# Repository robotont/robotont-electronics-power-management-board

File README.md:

# robotont-electronics-power-management-board
The repository contains schematics and PCB layout for the Robotont power management board.
The [production](Production/) folder contains prepared gerbers with pos file ready to order a from e.g. JLCPCB.

## Schematics

## Layout

The following figures visualize the front side of the board along with the 3D model of the design.

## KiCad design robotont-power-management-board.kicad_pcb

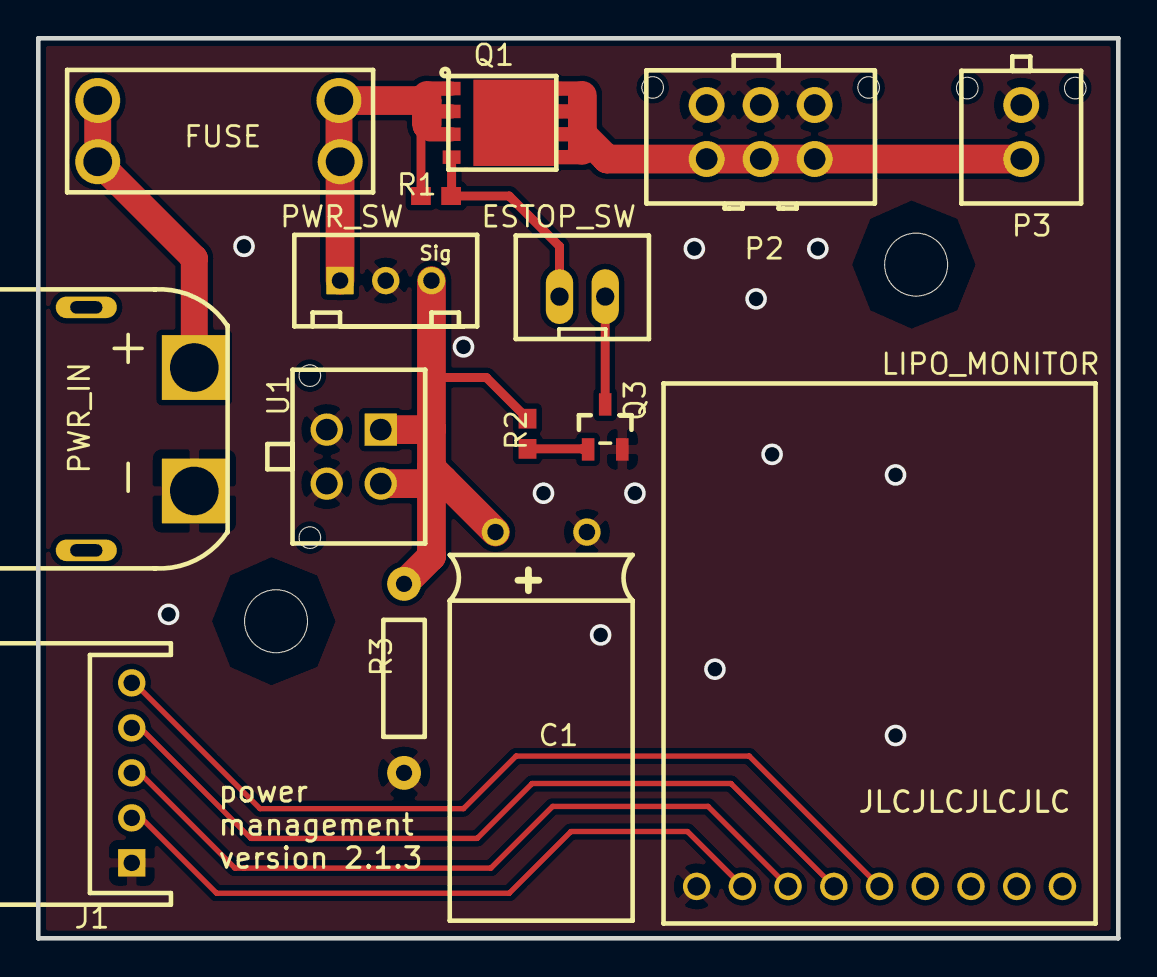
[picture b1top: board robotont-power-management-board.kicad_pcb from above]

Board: 2 copper layers, 60.0 x 50.0 mm, 15 parts (0 on the bottom side), 12 nets.

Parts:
C1: +; ELECTROLYTIC CAP HORIZONTAL 10X20MM
ESTOP_SW: 1; JST-XH-02-PACKAGE-LONG-PAD
FUSE: 30A; 3557-2
J1: S5B-XH-A(LF)(SN); JST-XH-S5B-XH-A
LIPO_MONITOR: LiPo Tester; LIPO_BATTERY_TESTER
P2: 430450627
P3: 430450212
PWR_IN: XT60PW-M; XT60PW-M PCBLIB
PWR_SW: Sig; JST-XH-3PIN TD
Q1: BSC030P03NS3G; SON-8_5MMX6MM
Q3: 2N7002-7-F; SOT-23-3_L2.9-W1.6-P1.90-LS2.8-BR
R1: 10k; 0603-RES
R2: 1k; 0603-RES
R3: 1.2K; RES-TH_BD2.3-L6.5-P10.50-D0.5
U1: 430450412; CONN-TH_4P-P3.00-S3.00_L7.4-W9.7-EH9.0

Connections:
C1_2: C1.2, PWR_SW.3, R2.1, R3.2, U1.1, U1.2
ESTOP_SW_1: ESTOP_SW.1, Q1.4, R1.2
ESTOP_SW_2: ESTOP_SW.2, Q3.3
FUSE_1: FUSE.1, PWR_IN.2
GND: C1.1, J1.1, LIPO_MONITOR.1, P2.4, P2.5, P2.6, P3.1, PWR_IN.1, PWR_SW.2, Q3.2, R3.1, U1.3, U1.4
J1_2: J1.2, LIPO_MONITOR.2
J1_3: J1.3, LIPO_MONITOR.3
J1_4: J1.4, LIPO_MONITOR.4
J1_5: J1.5, LIPO_MONITOR.5
Q1_5: P2.1, P2.2, P2.3, P3.2, Q1.5, Q1.6, Q1.7, Q1.8, Q1.9
R2_2: Q3.1, R2.2
VCC: FUSE.2, PWR_SW.1, Q1.1, Q1.2, Q1.3, R1.1

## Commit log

2021-10-05 pcb converted from easyeda
2021-10-05 added CERN OHL permissive license
2022-02-03 pasted in an image of easyeda schematic
2022-08-26 added production files
2023-03-10 bom txt -> csv
2023-03-10 Added some info and visuals to the readme
